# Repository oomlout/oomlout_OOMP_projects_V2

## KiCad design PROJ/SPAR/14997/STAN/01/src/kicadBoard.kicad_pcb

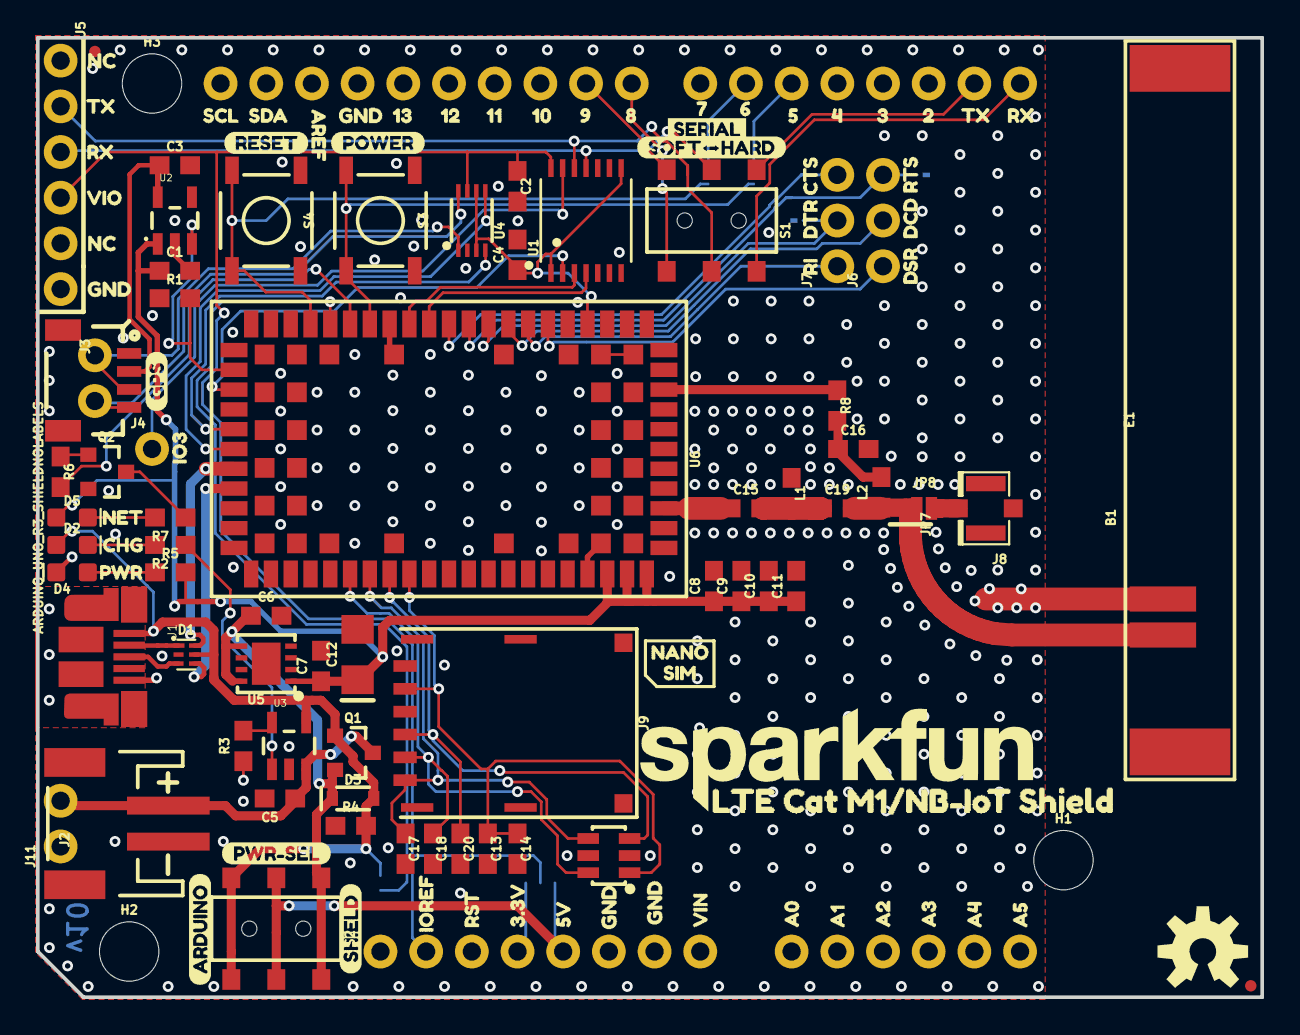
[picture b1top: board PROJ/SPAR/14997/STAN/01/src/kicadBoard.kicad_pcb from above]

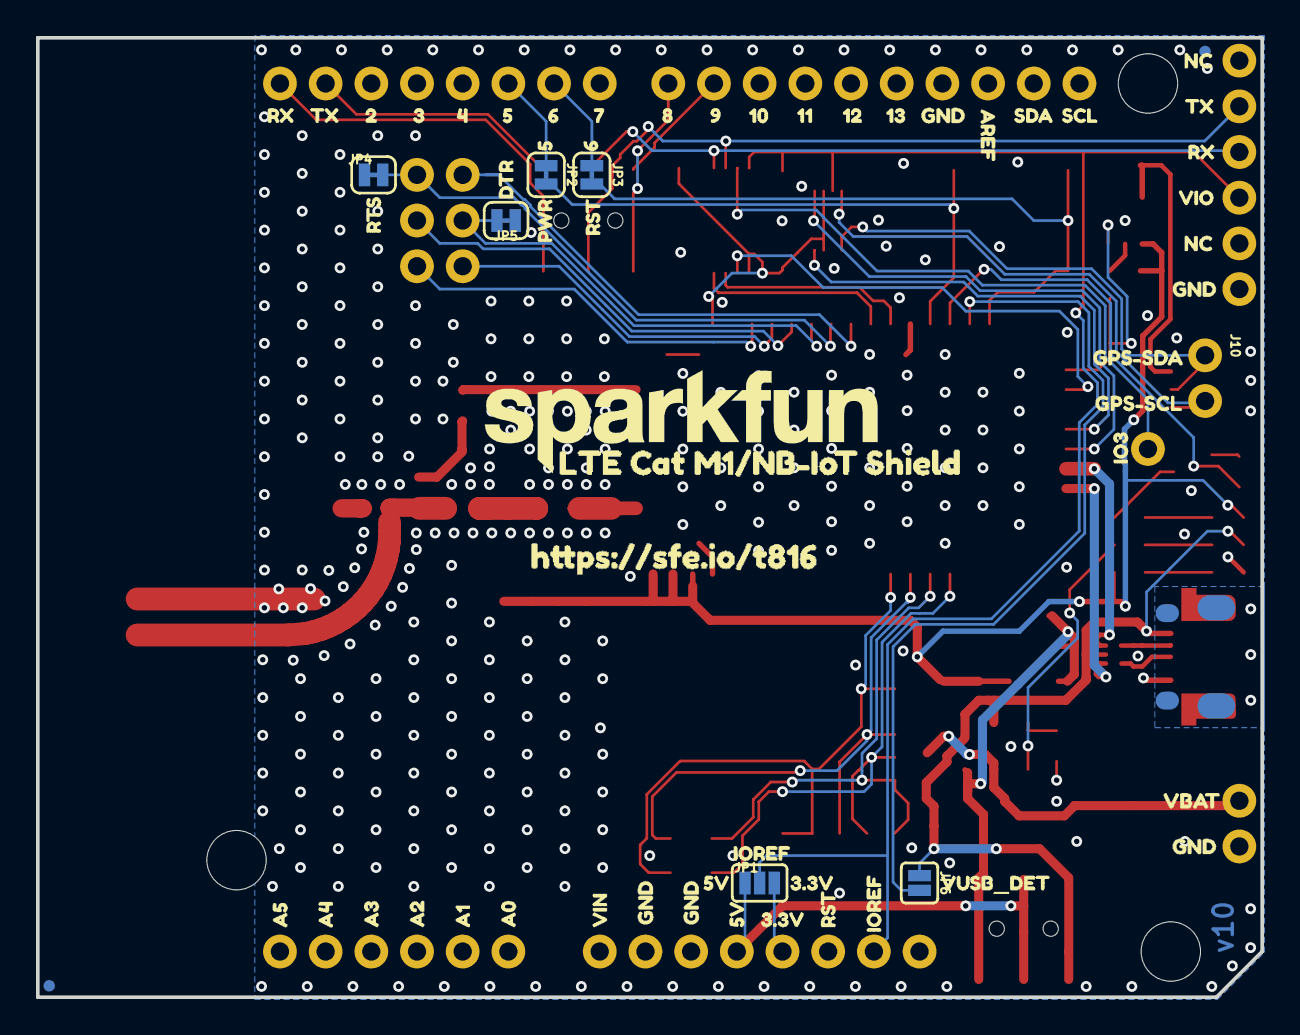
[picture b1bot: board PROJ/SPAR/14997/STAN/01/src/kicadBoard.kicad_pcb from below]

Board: 2 copper layers, 68.1 x 53.3 mm, 193 parts (64 on the bottom side), 60 nets.

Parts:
B1: ARDUINO_UNO_R3_SHIELDNOLABELS; UNO_R3_SHIELD_NOLABELS
C1, C3: 1.0uF; 0603
C2, C4, C8, C13: 0.1uF; 0603
C5, C6, C7: 4.7uF; 0603
C9: 10nF; 0603
C10, C15: 15pF; 0603
C11: 68pF; 0603
C12: 100uF; 1206-POLAR
C14, C17, C18, C20: 47pF; 0603
C16: DNP; 0603
C19: 0; 0603
D1: PRTR5V0U2F; SOT886
D2: Yellow; LED-0603
D3: 1A/23V/620mV; SOD-323
D4: RED; LED-0603
D5: BLUE; LED-0603
D6: DT1042-04SO-7; SOT23-6L
E1: MOLEX-146200; MOLEX_146200
FD1, FD2, FD3, FD4: FIDUCIALUFIDUCIAL; FIDUCIAL-MICRO
FRAME1, FRAME2: FRAME-LETTER; CREATIVE_COMMONS
H1, H2, H3: STAND-OFF
J1: USB-MICROB-PTH-MILL
J2: JST-2-SMD
J3: 1X04_1MM_RA
J4: 1X01_NO_SILK
J5: 1X06_NO_SILK
J6, J7: 1X03_NO_SILK
J8: U.FL
J9: NANO_SIM; NANO_SIM_WURTH_693043020611
J10, J11: 1X02_NO_SILK
JP1: IOREF-SEL; SMT-JUMPER_3_NO_SILK
JP2, JP3: JUMPER-SMT_2_NC_TRACE_SILK; SMT-JUMPER_2_NC_TRACE_SILK
JP4, JP5: SMT-JUMPER_2_NC_TRACE_SILK
JP6: VUSB_DET; SMT-JUMPER_2_NO_SILK
JP7: J-CHIP; SMT-JUMPER_2_NC_TRACE_NO-SILK
JP8: J-U.FL; SMT-JUMPER_2_NO_NO-SILK
L1: 39nH; 0603
L2: DNP; 0603
LOGO1, LOGO3: SFE_LOGO_NAME.2_INCH; SFE_LOGO_NAME_.2
LOGO2: OSHW-LOGOM; OSHW-LOGO-M
Q1: 2.5A/30V/105mΩ; SOT23-3
Q2: 600mA/40V; SOT23-3
R1: 47k; 0603
R2, R5, R7: 1k; 0603
R3: 2.0k; 0603
R4, R6: 10k; 0603
R8: DNP; 0603
S1, S2: SWITCH_DPDT_SMD_AYZ0202
S3: PWR_ON; TACTILE_SWITCH_SMD_5.2MM
S4: RESET; TACTILE_SWITCH_SMD_5.2MM
U1: TXB0104; TSSOP14
U2: AP2112K-3.3; SOT23-5
U3: MCP73831; SOT23-5
U4: TCA9406DCU; VSSOP-8
U5: AP7361C-33FGE; 8-UDFN
U6: SARA-R410M-2B; SARA-LGA
U$1, U$85: SCL0
U$2, U$84: SDA1
U$3, U$86: AREF2
U$4, U$45, U$46, U$73, U$74, U$88, U$104, U$105, U$112: GND3
U$5, U$87: 134
U$6, U$89: 125
U$7, U$90: 116
U$8, U$91: 107
U$9, U$92: 98
U$10, U$93: 89
U$11: RESET48
U$12: GPS47
U$13, U$94: 714
U$14, U$62, U$95: 615
U$15, U$61, U$96: 516
U$16, U$97: 417
U$17, U$98: 318
U$18, U$99: 219
U$19: POWER49
U$20, U$30, U$81, U$101: RX22
U$21, U$31, U$80, U$100: TX21
U$22: SERIAL57
U$23: CTS23
U$24, U$63: DTR24
U$25: RI25
U$26: DSR26
U$27: DCD27
U$28, U$64: RTS28
U$29, U$82: VIO29
U$32, U$77: LTE_CAT_M1#NB#IOT_SHIELD1
U$33: ARDUINO51
U$34, U$79: IO334
U$35: NET31
U$36: CHG33
U$37, U$59: PWR32
U$38: PWR#SEL53
U$39: SHIELD52
U$40, U$42: RST0
U$41, U$56, U$78: IOREF39
U$43, U$58, U$76: 3#3V41
U$44, U$57, U$75: 5V42
U$47, U$72: VIN43
U$48, U$71: A044
U$49, U$70: A145
U$50, U$69: A246
U$51, U$68: A347
U$52, U$67: A448
U$53, U$66: A549
U$54: NANO50
U$55: SIM51
U$60: RST40
U$65: VUSB_DET52
U$83: HTTPS###SFE#IO#T8160
U$102: SOFT#HARD50
U$103, U$106, U$107, U$108: NC0
U$109: GPS#SCL1
U$110: GPS#SDA0
U$111: VBAT2

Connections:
1.8V: C4.1, U1.1, U1.8, U4.3, U4.6, U6.4
3.3V: C1.1, C7.1, C8.1, C9.1, C10.1, C11.1, C12.1, D5.A, R5.2, U2.1, U5.1, U6.51, U6.52, U6.53
ANT: C15.1, U6.56
ANT_DET: R8.1, U6.62
ARDUINO-3.3V: B1.3.3V, JP1.3
ARDUINO-5V: B1.5V, JP1.1, S2.2, S2.5
CTS: J7.3, U6.11
D+: D1.4, U6.29
D-: D1.6, U6.28
DCD: J6.2, U6.8
DSR: J6.1, U6.6
DTR: J7.2, JP5.2, U6.9
GND: B1.AREF, B1.GND@0, B1.GND@1, B1.GND@2, C1.2, C2.2, C3.2, C4.2, C5.2, C6.2, C7.2, C8.2, C9.2, C10.2, C11.2, C12.2, C13.2, C14.2, C16.2, C17.2, C18.2, C20.2, D1.2, D4.C, D6.2, D6.5, E1.GND, J1.GND, J2.1, J3.1, J5.6, J8.1, J8.2, J9.C5, J11.1, JP4.1, JP5.1, L1.1, Q2.2, R1.1, R3.1, R4.1, S3.1, S3.2, S4.1, S4.2, U1.7, U2.2, U3.2, U4.2, U5.4, U5.EP, U6.1, U6.3, U6.5, U6.14, U6.20, U6.21, U6.22, U6.30, U6.32, U6.33, U6.43, U6.50, U6.54, U6.55, U6.57, U6.58, U6.59, U6.60, U6.61, U6.63, U6.64, U6.65, U6.66, U6.67, U6.68, U6.69, U6.70, U6.71, U6.72, U6.73, U6.74, U6.75, U6.76, U6.77, U6.78, U6.79, U6.80, U6.81, U6.82, U6.83, U6.84, U6.85, U6.86, U6.87, U6.88, U6.89, U6.90, U6.91, U6.92, U6.93, U6.94, U6.95, U6.96
GPIO1: R6.2, U6.16
GPIO2: R1.2, U2.3, U6.23
GPIO3-CELL: U1.2, U6.24
GPIO3-QWIIC: J4.1, U1.13
GPS-3.3V: C3.1, J3.2, U2.5
HARDRX-ARDUINO: B1.RX, S1.1
HARDTX-ARDUINO: B1.TX, S1.4
IOREF: B1.IOREF, C2.1, J5.4, JP1.2, U1.14, U4.7
unnamed: R3.2, U3.5
unnamed: C16.1, L2.2, R8.2
unnamed: C15.2, C19.1, L1.2
unnamed: J8.FEED, JP8.2
unnamed: Q2.1, R6.1
unnamed: D1.1, J1.D-
unnamed: D5.C, R7.2
unnamed: D1.3, J1.D+
unnamed: Q2.3, R7.1
unnamed: D4.A, R5.1
unnamed: D2.C, R2.2
unnamed: R2.1, U3.1
unnamed: B1.D5, JP2.1
unnamed: B1.D6, JP3.1
unnamed: C19.2, JP7.1, JP8.1, L2.1
unnamed: E1.FEED, JP7.2
PWR_ON: JP2.2, S3.3, S3.4, U6.15
RESET_N: JP3.2, S4.3, S4.4, U6.18
RI: J7.1, U6.7
RTS: J6.3, JP4.2, U6.10
RX-ARDUINO: J5.2, S1.2, U1.12
RX-CELL: U1.4, U6.12
SCL-CELL: U4.5, U6.27
SCL-QWIIC: J3.4, J10.2, U4.8
SDA-CELL: U4.4, U6.26
SDA-QWIIC: J3.3, J10.1, U4.1
SHIELD: J1.SHIELD, J1.SHIELD2, J1.SHIELD3, J1.SHIELD4, J1.SHIELD5, J1.SHIELD6, J1.SHIELD7, J1.SHIELD8, J1.SHIELD9, J1.SHIELD10
SIM_CLK: C18.1, D6.6, J9.C3, U6.38
SIM_IO: C17.1, D6.4, J9.C7, U6.39
SIM_RST: C20.1, D6.3, J9.C2, U6.40
SOFTRX-ARDUINO: B1.D8, S1.3
SOFTTX-ARDUINO: B1.D9, S1.6
TX-ARDUINO: J5.3, S1.5, U1.11
TX-CELL: U1.3, U6.13
VIN: C6.1, D3.C, Q1.2, S2.1, S2.4, U5.5, U5.8
VSIM: C13.1, C14.1, D6.1, J9.C1, U6.41
VUSB_DET: JP6.2, U6.17
V_BATT: C5.1, J2.2, J11.2, Q1.3, U3.3
V_USB: D1.5, D2.A, D3.A, J1.VBUS, JP6.1, Q1.1, R4.2, S2.3, S2.6, U3.4

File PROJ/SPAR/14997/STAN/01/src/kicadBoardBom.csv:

"Id";"Designator";"Package";"Quantity";"Designation";"Supplier and ref";
1;"U$16,U$97";"417";2;"";;;
2;"U$7,U$90";"116";2;"";;;
3;"J2";"JST-2-SMD";1;"";;;
4;"C12";"1206-POLAR";1;"100uF";;;
5;"FD4,FD3,FD2,FD1";"FIDUCIAL-MICRO";4;"FIDUCIALUFIDUCIAL";;;
6;"U$22";"SERIAL57";1;"";;;
7;"C11";"0603";1;"68pF";;;
8;"U$107,U$103,U$106,U$108";"NC0";4;"";;;
9;"U$26";"DSR26";1;"";;;
10;"U1";"TSSOP14";1;"TXB0104";;;
11;"U$1,U$85";"SCL0";2;"";;;
12;"D6";"SOT23-6L";1;"DT1042-04SO-7";;;
13;"U$9,U$92";"98";2;"";;;
14;"H1,H2,H3";"STAND-OFF";3;"STAND-OFF";;;
15;"C5,C7,C6";"0603";3;"4.7uF";;;
16;"U$37,U$59";"PWR32";2;"";;;
17;"U$54";"NANO50";1;"";;;
18;"U$4,U$46,U$45,U$104,U$73,U$112,U$88,U$105,U$74";"GND3";9;"";;;
19;"U$20,U$30,U$81,U$101";"RX22";4;"";;;
20;"U4";"VSSOP-8";1;"TCA9406DCU";;;
21;"L2,C16,R8";"0603";3;"DNP";;;
22;"LOGO2";"OSHW-LOGO-M";1;"OSHW-LOGOM";;;
23;"U$2,U$84";"SDA1";2;"";;;
24;"LOGO1,LOGO3";"SFE_LOGO_NAME_.2";2;"SFE_LOGO_NAME.2_INCH";;;
25;"U$41,U$78,U$56";"IOREF39";3;"";;;
26;"U$24,U$63";"DTR24";2;"";;;
27;"C15,C10";"0603";2;"15pF";;;
28;"C18,C20,C17,C14";"0603";4;"47pF";;;
29;"U$43,U$76,U$58";"3#3V41";3;"";;;
30;"JP8";"SMT-JUMPER_2_NO_NO-SILK";1;"J-U.FL";;;
31;"U$18,U$99";"219";2;"";;;
32;"J7,J6";"1X03_NO_SILK";2;"";;;
33;"FRAME2,FRAME1";"CREATIVE_COMMONS";2;"FRAME-LETTER";;;
34;"U$51,U$68";"A347";2;"";;;
35;"C13,C8,C2,C4";"0603";4;"0.1uF";;;
36;"U$21,U$31,U$80,U$100";"TX21";4;"";;;
37;"U$12";"GPS47";1;"";;;
38;"U$28,U$64";"RTS28";2;"";;;
39;"U$53,U$66";"A549";2;"";;;
40;"U$52,U$67";"A448";2;"";;;
41;"R1";"0603";1;"47k";;;
42;"D3";"SOD-323";1;"1A/23V/620mV";;;
43;"U$47,U$72";"VIN43";2;"";;;
44;"U$14,U$62,U$95";"615";3;"";;;
45;"B1";"UNO_R3_SHIELD_NOLABELS";1;"ARDUINO_UNO_R3_SHIELDNOLABELS";;;
46;"E1";"MOLEX_146200";1;"MOLEX-146200";;;
47;"U$27";"DCD27";1;"";;;
48;"U$23";"CTS23";1;"";;;
49;"U$38";"PWR#SEL53";1;"";;;
50;"U$10,U$93";"89";2;"";;;
51;"D4";"LED-0603";1;"RED";;;
52;"U6";"SARA-LGA";1;"SARA-R410M-2B";;;
53;"U$15,U$96,U$61";"516";3;"";;;
54;"U$17,U$98";"318";2;"";;;
55;"U$39";"SHIELD52";1;"";;;
56;"JP7";"SMT-JUMPER_2_NC_TRACE_NO-SILK";1;"J-CHIP";;;
57;"J9";"NANO_SIM_WURTH_693043020611";1;"NANO_SIM";;;
58;"J11,J10";"1X02_NO_SILK";2;"";;;
59;"U$8,U$91";"107";2;"";;;
60;"R6,R4";"0603";2;"10k";;;
61;"U$3,U$86";"AREF2";2;"";;;
62;"U$5,U$87";"134";2;"";;;
63;"U3";"SOT23-5";1;"MCP73831";;;
64;"U$50,U$69";"A246";2;"";;;
65;"J1";"USB-MICROB-PTH-MILL";1;"";;;
66;"U$33";"ARDUINO51";1;"";;;
67;"Q1";"SOT23-3";1;"2.5A/30V/105mΩ";;;
68;"D5";"LED-0603";1;"BLUE";;;
69;"U$44,U$57,U$75";"5V42";3;"";;;
70;"S3";"TACTILE_SWITCH_SMD_5.2MM";1;"PWR_ON";;;
71;"U5";"8-UDFN";1;"AP7361C-33FGE";;;
72;"C9";"0603";1;"10nF";;;
73;"U$29,U$82";"VIO29";2;"";;;
74;"R3";"0603";1;"2.0k";;;
75;"C19";"0603";1;"0";;;
76;"U$48,U$71";"A044";2;"";;;
77;"U$13,U$94";"714";2;"";;;
78;"R5,R2,R7";"0603";3;"1k";;;
79;"C1,C3";"0603";2;"1.0uF";;;
80;"J8";"U.FL";1;"U.FL";;;
81;"Q2";"SOT23-3";1;"600mA/40V";;;
82;"U$25";"RI25";1;"";;;
83;"D1";"SOT886";1;"PRTR5V0U2F";;;
84;"U$49,U$70";"A145";2;"";;;
85;"J3";"1X04_1MM_RA";1;"";;;
86;"U$102";"SOFT#HARD50";1;"";;;
87;"U$11";"RESET48";1;"";;;
88;"U$77,U$32";"LTE_CAT_M1#NB#IOT_SHIELD1";2;"";;;
89;"S1,S2";"SWITCH_DPDT_SMD_AYZ0202";2;"";;;
90;"L1";"0603";1;"39nH";;;
91;"U$34,U$79";"IO334";2;"";;;
92;"U2";"SOT23-5";1;"AP2112K-3.3";;;
93;"J5";"1X06_NO_SILK";1;"";;;
94;"U$19";"POWER49";1;"";;;
95;"D2";"LED-0603";1;"Yellow";;;
96;"U$55";"SIM51";1;"";;;
97;"J4";"1X01_NO_SILK";1;"";;;
98;"U$6,U$89";"125";2;"";;;
99;"U$35";"NET31";1;"";;;
100;"U$36";"CHG33";1;"";;;
101;"U$40,U$42";"RST0";2;"";;;
102;"S4";"TACTILE_SWITCH_SMD_5.2MM";1;"RESET";;;
103;"U$111";"VBAT2";1;"";;;
104;"JP1";"SMT-JUMPER_3_NO_SILK";1;"IOREF-SEL";;;
105;"U$60";"RST40";1;"";;;
106;"JP5,JP4";"SMT-JUMPER_2_NC_TRACE_SILK";2;"";;;
107;"JP3,JP2";"SMT-JUMPER_2_NC_TRACE_SILK";2;"JUMPER-SMT_2_NC_TRACE_SILK";;;
108;"JP6";"SMT-JUMPER_2_NO_SILK";1;"VUSB_DET";;;
109;"U$110";"GPS#SDA0";1;"";;;
110;"U$65";"VUSB_DET52";1;"";;;
111;"U$109";"GPS#SCL1";1;"";;;
112;"U$83";"HTTPS###SFE#IO#T8160";1;"";;;

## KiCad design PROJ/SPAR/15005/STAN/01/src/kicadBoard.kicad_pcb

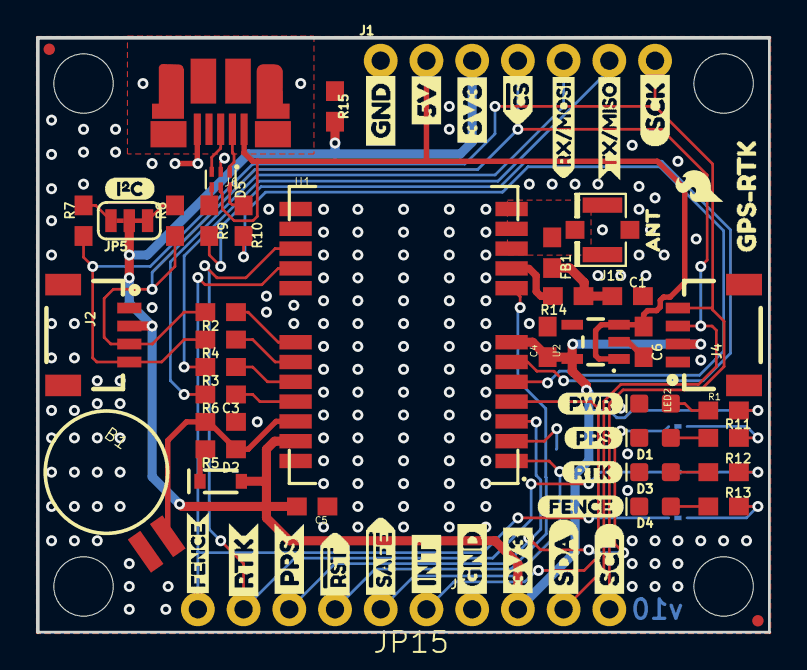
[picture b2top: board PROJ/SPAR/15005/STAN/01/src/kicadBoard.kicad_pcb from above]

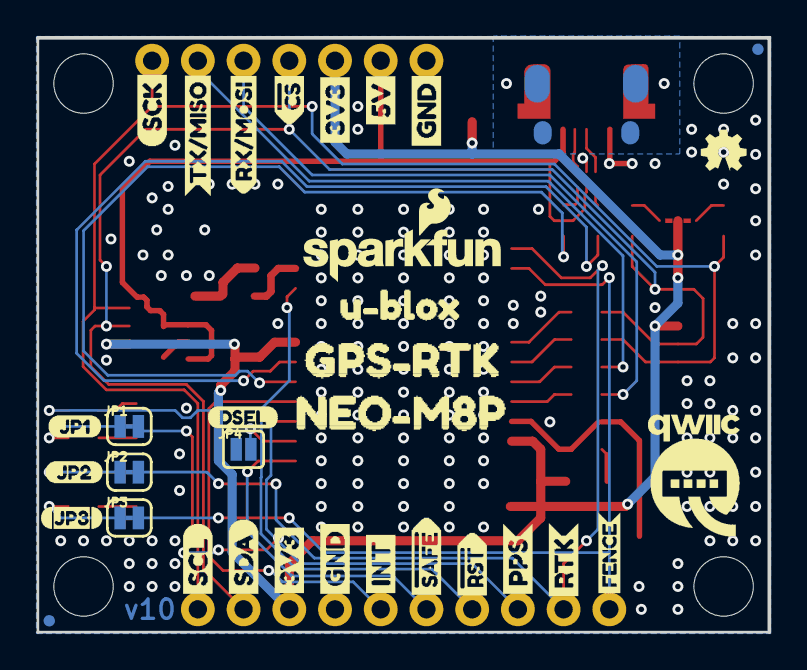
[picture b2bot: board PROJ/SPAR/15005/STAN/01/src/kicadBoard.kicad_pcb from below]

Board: 2 copper layers, 40.6 x 33.0 mm, 103 parts (33 on the bottom side), 39 nets.

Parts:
B1: 6.8MM_COIN_CELL; BATTCON-6.8MM
C1: 47pF; 0603
C3, C4, C6: 1.0uF; 0603
C5: 0.1uF; 0603
D1: Yellow; LED-0603
D2: 0.5A/40V/420mV; SOD-323
D3: GREEN; LED-0603
D4: BLUE; LED-0603
D5: PRTR5V0U2F; SOT886
FB1: 30Ω/1.8A; 0603
FRAME1: FRAME-LETTER; CREATIVE_COMMONS
J1: 1X07_NO_SILK
J2, J4: Qwiic Right Angle; 1X04_1MM_RA
J3: PTH; 1X04_NO_SILK
J6: USB-MICROB-PTH-MILL
J13: U.FL
JP1, JP2, JP3: SMT-JUMPER_2_NC_TRACE_SILK
JP4: SMT-JUMPER_2_NO_SILK
JP5: SMT-JUMPER_3_2-NC_TRACE_SILK
JP15: 1X06_NO_SILK
JP21, JP61, JP71, JP81: FIDUCIALUFIDUCIAL; MICRO-FIDUCIAL
JP31, JP41, JP91, JP101: STAND-OFF
LED2: RED; LED-0603
LOGO1: OSHW-LOGOMINI; OSHW-LOGO-MINI
LOGO2: SFE_LOGO_NAME_FLAME.1_INCH; SFE_LOGO_NAME_FLAME_.1
R1, R5, R11, R12, R13: 1k; 0603
R2, R3, R4, R6: 33; 0603
R7, R8: 2.2k; 0603
R9, R10: 27; 0603
R14: 10; 0603
R15: 100k; 0603
U1: NEO-M8P
U2: 3.3V; SOT23-5
U$1, U$4: SDA-[)
U$3, U$5: SCL-[)
U$6, U$7, U$60, U$61: 3V3-04
U$8, U$9, U$62, U$63: GND-04
U$10: I_SUPER2_C-()-03
U$11: FENCE2
U$12: JP20
U$13, U$28, U$29: RTK1
U$14, U$17: FENCE0
U$15, U$16: INT8
U$18: PWR-()-03
U$19, U$20: 5V
U$21: GPS#RTK0
U$22: U#BLOX3
U$23, U$24: CS#-_]
U$25: JP10
U$26: RX#MOSI2
U$27: DSEL0
U$30: QWIIC-LOGO-MEDIUM
U$31: RX#MOSI3
U$32: JP32
U$33: SFE_LOGO_FLAME_.1
U$34: TX#MISO0
U$35, U$36: #RST3
U$37: TX#MISO1
U$38, U$41: SCK-(]-04
U$39, U$40: #SAFE1
U$43, U$44: PPS5
U$52: PPS0
U$53: NEO#M8P3
U$54: GPS#RTK1
U$55: ANT0

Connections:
3.3V: C4.1, C5.2, D2.A, J1.3, J2.2, J3.2, J4.2, JP5.2, R1.2, R15.2, U1.7, U1.23, U2.5
5V: C6.1, D5.5, J1.2, J6.VBUS, U2.1, U2.3
ANT_VCC: C1.1, FB1.2, R14.1
BACKUP: B1.+, C3.1, R5.1, U1.22
D+: D5.4, R9.1
D-: D5.6, R10.1
D_SEL: JP4.2, U1.2
FENCE_STAT: JP3.2, JP15.6, U1.16
GND: B1.-, C1.2, C3.2, C4.2, C5.1, C6.2, D1.C, D3.C, D4.C, D5.2, J1.1, J2.1, J3.1, J4.1, J6.GND, J13.1, J13.2, JP4.1, LED2.C, R15.1, U1.10, U1.12, U1.13, U1.24, U2.2
GPS_ANT1: FB1.1, J13.FEED, U1.11
INT: JP15.1, U1.4
unnamed: D3.A, R12.1
unnamed: D1.A, R11.1
unnamed: JP2.1, R12.2
unnamed: JP1.1, R11.2
unnamed: JP5.1, R8.2
unnamed: D2.C, R5.2
unnamed: D4.A, R13.1
unnamed: JP5.3, R7.2
unnamed: JP3.1, R13.2
unnamed: LED2.A, R1.1
unnamed: R9.2, U1.6
unnamed: R10.2, U1.5
unnamed: R14.2, U1.9
PPS: JP1.2, JP15.4, U1.3
RTK_STAT: JP2.2, JP15.5, U1.15
RXI/MOSI: J1.5, R6.2
RXLV: R6.1, U1.21
SCL/SCK: J1.7, J2.4, J3.4, J4.4, R4.2, R7.1
SCL_LV: R4.1, U1.19
SDA/~CS: J1.4, J2.3, J3.3, J4.3, R2.2, R8.1
SDA_LV: R2.1, U1.18
SHLD: J6.SHIELD, J6.SHIELD2, J6.SHIELD3, J6.SHIELD4, J6.SHIELD5, J6.SHIELD6, J6.SHIELD7, J6.SHIELD8, J6.SHIELD9, J6.SHIELD10
TXLV: R3.1, U1.20
TXO/MISO: J1.6, R3.2
USB_D+: D5.3, J6.D+
USB_D-: D5.1, J6.D-
~RESET: JP15.3, U1.8
~SAFE: JP15.2, U1.1

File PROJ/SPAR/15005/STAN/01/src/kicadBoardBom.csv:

"Id";"Designator";"Package";"Quantity";"Designation";"Supplier and ref";
1;"J13";"U.FL";1;"U.FL";;;
2;"U1";"NEO-M8P";1;"NEO-M8P";;;
3;"U$6,U$61,U$7,U$60";"3V3-04";4;"";;;
4;"C6,C3,C4";"0603";3;"1.0uF";;;
5;"D2";"SOD-323";1;"0.5A/40V/420mV";;;
6;"U$10";"I_SUPER2_C-()-03";1;"";;;
7;"FRAME1";"CREATIVE_COMMONS";1;"FRAME-LETTER";;;
8;"R4,R6,R2,R3";"0603";4;"33";;;
9;"U$13,U$29,U$28";"RTK1";3;"";;;
10;"JP21,JP61,JP81,JP71";"MICRO-FIDUCIAL";4;"FIDUCIALUFIDUCIAL";;;
11;"D4";"LED-0603";1;"BLUE";;;
12;"J1";"1X07_NO_SILK";1;"";;;
13;"U$23,U$24";"CS#-_]";2;"";;;
14;"R13,R11,R1,R5,R12";"0603";5;"1k";;;
15;"J3";"1X04_NO_SILK";1;"PTH";;;
16;"U$8,U$63,U$62,U$9";"GND-04";4;"";;;
17;"U$38,U$41";"SCK-(]-04";2;"";;;
18;"C5";"0603";1;"0.1uF";;;
19;"JP91,JP41,JP101,JP31";"STAND-OFF";4;"STAND-OFF";;;
20;"U$1,U$4";"SDA-[)";2;"";;;
21;"U$35,U$36";"#RST3";2;"";;;
22;"D1";"LED-0603";1;"Yellow";;;
23;"B1";"BATTCON-6.8MM";1;"6.8MM_COIN_CELL";;;
24;"C1";"0603";1;"47pF";;;
25;"JP5";"SMT-JUMPER_3_2-NC_TRACE_SILK";1;"";;;
26;"R8,R7";"0603";2;"2.2k";;;
27;"FB1";"0603";1;"30Ω/1.8A";;;
28;"U$3,U$5";"SCL-[)";2;"";;;
29;"U$52";"PPS0";1;"";;;
30;"J6";"USB-MICROB-PTH-MILL";1;"";;;
31;"U$19,U$20";"5V";2;"";;;
32;"U$21";"GPS#RTK0";1;"";;;
33;"U$11";"FENCE2";1;"";;;
34;"U$33";"SFE_LOGO_FLAME_.1";1;"";;;
35;"U$15,U$16";"INT8";2;"";;;
36;"U$26";"RX#MOSI2";1;"";;;
37;"U$43,U$44";"PPS5";2;"";;;
38;"U$18";"PWR-()-03";1;"";;;
39;"J4,J2";"1X04_1MM_RA";2;"Qwiic Right Angle";;;
40;"R9,R10";"0603";2;"27";;;
41;"U$34";"TX#MISO0";1;"";;;
42;"D5";"SOT886";1;"PRTR5V0U2F";;;
43;"U$55";"ANT0";1;"";;;
44;"U$39,U$40";"#SAFE1";2;"";;;
45;"R15";"0603";1;"100k";;;
46;"U2";"SOT23-5";1;"3.3V";;;
47;"R14";"0603";1;"10";;;
48;"LED2";"LED-0603";1;"RED";;;
49;"U$14,U$17";"FENCE0";2;"";;;
50;"D3";"LED-0603";1;"GREEN";;;
51;"JP15";"1X06_NO_SILK";1;"";;;
52;"JP3,JP2,JP1";"SMT-JUMPER_2_NC_TRACE_SILK";3;"";;;
53;"LOGO1";"OSHW-LOGO-MINI";1;"OSHW-LOGOMINI";;;
54;"U$31";"RX#MOSI3";1;"";;;
55;"LOGO2";"SFE_LOGO_NAME_FLAME_.1";1;"SFE_LOGO_NAME_FLAME.1_INCH";;;
56;"JP4";"SMT-JUMPER_2_NO_SILK";1;"";;;
57;"U$12";"JP20";1;"";;;
58;"U$25";"JP10";1;"";;;
59;"U$37";"TX#MISO1";1;"";;;
60;"U$30";"QWIIC-LOGO-MEDIUM";1;"";;;
61;"U$54";"GPS#RTK1";1;"";;;
62;"U$32";"JP32";1;"";;;
63;"U$53";"NEO#M8P3";1;"";;;
64;"U$27";"DSEL0";1;"";;;
65;"U$22";"U#BLOX3";1;"";;;

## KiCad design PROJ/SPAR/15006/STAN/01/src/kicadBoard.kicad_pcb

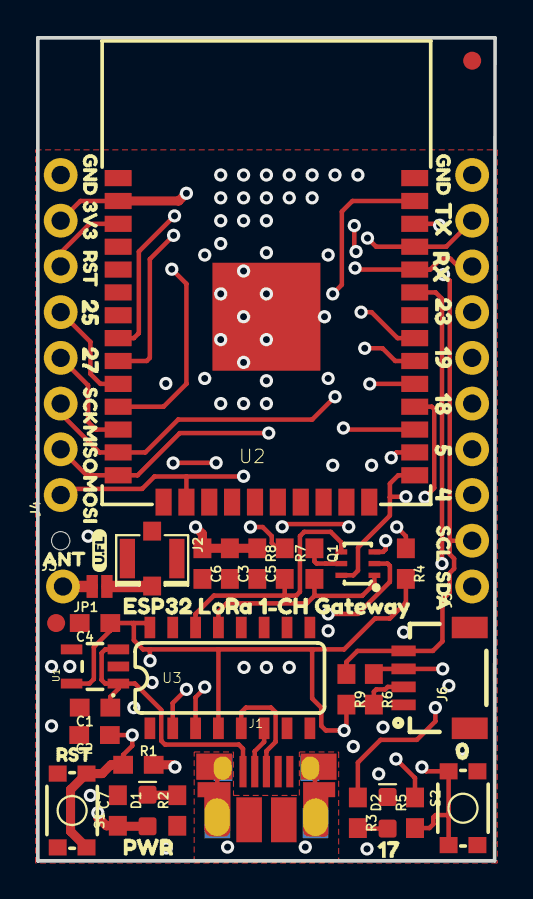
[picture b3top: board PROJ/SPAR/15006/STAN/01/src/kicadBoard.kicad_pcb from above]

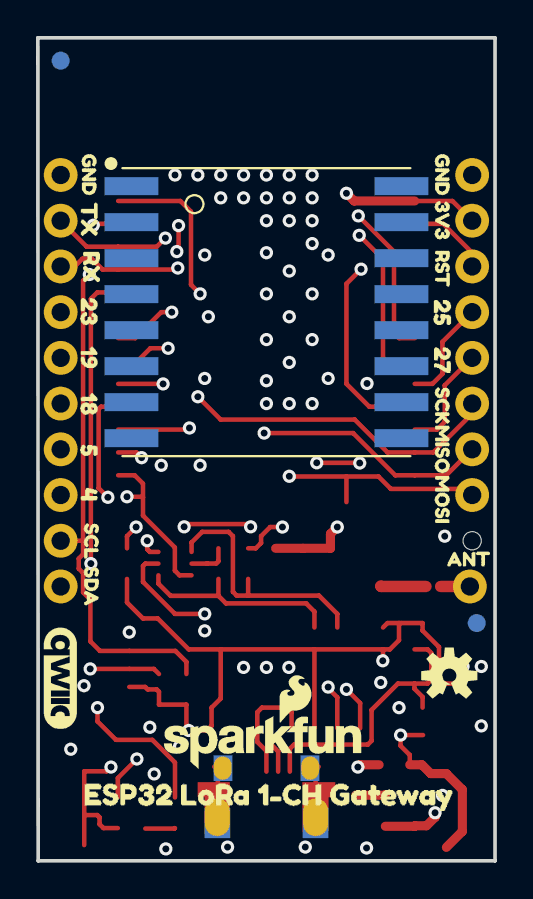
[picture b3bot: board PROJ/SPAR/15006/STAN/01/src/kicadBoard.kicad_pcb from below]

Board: 4 copper layers, 25.4 x 45.7 mm, 87 parts (26 on the bottom side), 36 nets.

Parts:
@HOLE0: (no value)
C1, C4: 1.0uF; 0603
C2, C3, C7: 0.1uF; 0603
C5: 10uF; 0603
C6: 4.7uF; 0603
D1: RED; LED-0603
D2: BLUE; LED-0603
FD1, FD2, FD3, FD4: FIDUCIAL1X2; FIDUCIAL-1X2
FRAME1: FRAME-LETTER; CREATIVE_COMMONS
J1: USB; USB-MICROB-PTH-MILL
J2: U.FL
J3: 1X01_NO_SILK
J4: 1X08_NO_SILK
J5: 1X10_NO_SILK
J6: QWIIC; 1X04_1MM_RA
JP1: Ant Sel; SMT-JUMPER_2_NO_NO-SILK
LOGO1: REVISION
LOGO2: SFE_LOGO_NAME_FLAME.1_INCH; SFE_LOGO_NAME_FLAME_.1
LOGO3: OSHW-LOGOS; OSHW-LOGO-S
Q1: MBT3904DW1T1; SC70-6
R1, R4, R5, R7, R8: 10k; 0603
R2, R3: 1k; 0603
R6, R9: 2.2k; 0603
S1: RESET; TACTILE_SWITCH_SMD_4.6X2.8MM
S2: 0; TACTILE_SWITCH_SMD_4.6X2.8MM
U1: 3.3V; SOT23-5
U2: ESP-WROOM-32NARROW; ESP-WROOM-32-NARROW
U3: CH340C; SO016
U4: RFM95W; RFM95_96_97_98W
U$1, U$10, U$26, U$37: GND0
U$2, U$38: 3V31
U$3, U$20, U$39: RST2
U$4, U$40: 2517
U$5, U$41: 279
U$6, U$42: SCK3
U$7, U$43: MISO4
U$8, U$44: MOSI5
U$9, U$36: ANT6
U$11, U$27: TX16
U$12, U$28: RX15
U$13, U$29: 2314
U$14, U$30: 1912
U$15, U$31: 1811
U$16, U$32: 513
U$17, U$33: 410
U$18, U$34: SCL8
U$19, U$35: SDA7
U$21: 020
U$22: PWR19
U$23: 1722
U$24: U#FL0
U$25: ESP32_LORA_1#CH_GATEWAY21
U$45: ESP32_LORA_1#CH_GATEWAY23
U$46: QWIIC_COPYRIGHT_SMALL

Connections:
0: Q1.6, R5.1, S2.3, S2.4, U2.25
3.3V: C3.1, C4.1, C5.1, C6.1, C7.1, D1.A, J4.7, J6.2, R1.2, R4.2, R5.2, R6.2, R9.2, U1.5, U2.2, U3.4, U3.16, U4.3.3V
ANT: J3.1, JP1.2, U4.ANT
D+: J1.D+, U3.5
D-: J1.D-, U3.6
GND: C1.2, C2.2, C3.2, C4.2, C5.2, C6.2, C7.2, D2.C, J1.GND, J2.1, J2.2, J4.8, J5.10, J6.1, R2.1, S1.1, S1.2, S2.1, S2.2, U1.2, U2.1, U2.15, U2.38, U2.GND, U3.1, U4.GND@1, U4.GND@2, U4.GND@3
IO4: J5.3, U2.26
IO5: J5.4, U2.29
IO17: R3.1, U2.28
IO18: J5.5, U2.30
IO19: J5.6, U2.31
IO23: J5.7, U2.37
IO25: J4.5, U2.10
IO27: J4.4, U2.12
MISO: J4.2, U2.14, U4.MISO
MOSI: J4.1, U2.16, U4.MOSI
unnamed: D1.C, R2.2
unnamed: D2.A, R3.2
unnamed: J2.FEED, JP1.1
unnamed: Q1.5, R7.2
unnamed: Q1.2, R8.2
RESET: C2.1, J4.6, Q1.3, R1.1, S1.3, S1.4, U2.3
RFM_CS: U2.27, U4.NSS
RFM_DIO1/33: U2.9, U4.DIO1
RFM_DIO2/32: U2.8, U4.DIO2
RFM_INT/26: U2.11, U4.DIO0
RFM_RST: R4.1, U4.!RESET
RXI: J5.8, U2.34, U3.2
SCK: J4.3, U2.13, U4.SCK
SCL: J5.2, J6.4, R9.1, U2.36
SDA: J5.1, J6.3, R6.1, U2.33
SHIELD: J1.SHIELD, J1.SHIELD2, J1.SHIELD3, J1.SHIELD4, J1.SHIELD5, J1.SHIELD6, J1.SHIELD7, J1.SHIELD8, J1.SHIELD9, J1.SHIELD10
TXO: J5.9, U2.35, U3.3
V_USB: C1.1, J1.VBUS, U1.1, U1.3
~DTR: Q1.1, R7.1, U3.13
~RTS: Q1.4, R8.1, U3.14

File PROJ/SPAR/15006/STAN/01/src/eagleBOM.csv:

"Part";"Value";"Device";"Package";"Description";"PROD_ID";"SF_ID";"VALUE";
"C1";"1.0uF";"1.0UF-0603-16V-10%";"0603";"1µF ceramic capacitors";"CAP-00868";"";"1.0uF";
"C2";"0.1uF";"0.1UF-0603-25V-(+80/-20%)";"0603";"0.1µF ceramic capacitors";"CAP-00810";"";"0.1uF";
"C3";"0.1uF";"0.1UF-0603-25V-(+80/-20%)";"0603";"0.1µF ceramic capacitors";"CAP-00810";"";"0.1uF";
"C4";"1.0uF";"1.0UF-0603-16V-10%";"0603";"1µF ceramic capacitors";"CAP-00868";"";"1.0uF";
"C5";"10uF";"10UF-0603-6.3V-20%";"0603";"10.0µF ceramic capacitors";"CAP-11015";"";"10uF";
"C6";"4.7uF";"4.7UF-0603-6.3V-(10%)";"0603";"4.7µF ceramic capacitors";"CAP-08280";"";"4.7uF";
"C7";"0.1uF";"0.1UF-0603-25V-5%";"0603";"0.1µF ceramic capacitors";"CAP-08604";"";"0.1uF";
"D1";"RED";"LED-RED0603";"LED-0603";"Red SMD LED";"DIO-00819";"";"RED";
"D2";"BLUE";"LED-BLUE0603";"LED-0603";"Blue SMD LED";"DIO-08575";"";"BLUE";
"FD1";"FIDUCIAL1X2";"FIDUCIAL1X2";"FIDUCIAL-1X2";"Fiducial Alignment Points";"";"";"";
"FD2";"FIDUCIAL1X2";"FIDUCIAL1X2";"FIDUCIAL-1X2";"Fiducial Alignment Points";"";"";"";
"FD3";"FIDUCIAL1X2";"FIDUCIAL1X2";"FIDUCIAL-1X2";"Fiducial Alignment Points";"";"";"";
"FD4";"FIDUCIAL1X2";"FIDUCIAL1X2";"FIDUCIAL-1X2";"Fiducial Alignment Points";"";"";"";
"FRAME1";"FRAME-LETTER";"FRAME-LETTER";"CREATIVE_COMMONS";"Schematic Frame - Letter";"";"";"";
"J1";"USB";"USB_MICRO-B_HALF_PTH_MILL";"USB-MICROB-PTH-MILL";"USB Type Micro-B Connector";"CONN-13711";"";"";
"J2";"U.FL";"U.FL";"U.FL";"SMD Antenna Connector - U.FL";"CONN-09193";"WRL-09144";"U.FL";
"J3";"";"CONN_01PTH_NO_SILK_YES_STOP";"1X01_NO_SILK";"Single connection point. Often used as Generic Header-pin footprint for 0.1 inch spaced/style header connections";"";"";"";
"J4";"";"CONN_08NO_SILK_FEMALE_PTH";"1X08_NO_SILK";"Multi connection point. Often used as Generic Header-pin footprint for 0.1 inch spaced/style header connections";"CONN-08438";"";"";
"J5";"";"CONN_10NO_SILK_PTH_FEMALE";"1X10_NO_SILK";"Multi connection point. Often used as Generic Header-pin footprint for 0.1 inch spaced/style header connections";"CONN-11563";"";"";
"J6";"QWIIC";"QWIIC_CONNECTORJS-1MM";"1X04_1MM_RA";"SparkFun I2C Standard Qwiic Connector";"CONN-13694";"";"";
"JP1";"Ant Sel";"JUMPER-SMT_2_NO_NO-SILK";"SMT-JUMPER_2_NO_NO-SILK";"Normally open jumper";"";"";"";
"LOGO1";"REVISION";"REVISION";"REVISION";""Revision By" Text";"";"";"";
"LOGO2";"SFE_LOGO_NAME_FLAME.1_INCH";"SFE_LOGO_NAME_FLAME.1_INCH";"SFE_LOGO_NAME_FLAME_.1";"SparkFun Font Logo w/ Flame";"";"";"";
"LOGO3";"OSHW-LOGOS";"OSHW-LOGOS";"OSHW-LOGO-S";"Open-Source Hardware (OSHW) Logo";"";"";"";
"Q1";"MBT3904DW1T1";"TRANS_NPN_DUAL-MBT3904DW1T1";"SC70-6";"Dual NPN Transistors in Single Package";"TRANS-13337";"";"";
"R1";"10k";"10KOHM-0603-1/10W-1%";"0603";"10kΩ resistor";"RES-00824";"";"10k";
"R2";"1k";"1KOHM-0603-1/10W-1%";"0603";"1kΩ resistor";"RES-07856";"";"1k";
"R3";"1k";"1KOHM-0603-1/10W-1%";"0603";"1kΩ resistor";"RES-07856";"";"1k";
"R4";"10k";"10KOHM-0603-1/10W-1%";"0603";"10kΩ resistor";"RES-00824";"";"10k";
"R5";"10k";"10KOHM-0603-1/10W-1%";"0603";"10kΩ resistor";"RES-00824";"";"10k";
"R6";"2.2k";"2.2KOHM-0603-1/10W-1%";"0603";"2.2kΩ resistor";"RES-08272";"";"2.2k";
"R7";"10k";"10KOHM-0603-1/10W-1%";"0603";"10kΩ resistor";"RES-00824";"";"10k";
"R8";"10k";"10KOHM-0603-1/10W-1%";"0603";"10kΩ resistor";"RES-00824";"";"10k";
"R9";"2.2k";"2.2KOHM-0603-1/10W-1%";"0603";"2.2kΩ resistor";"RES-08272";"";"2.2k";
"S1";"RESET";"MOMENTARY-SWITCH-SPST-SMD-4.6X2.8MM";"TACTILE_SWITCH_SMD_4.6X2.8MM";"Momentary Switch (Pushbutton) - SPST";"SWCH-15606";"";"";
"S2";"0";"MOMENTARY-SWITCH-SPST-SMD-4.6X2.8MM";"TACTILE_SWITCH_SMD_4.6X2.8MM";"Momentary Switch (Pushbutton) - SPST";"SWCH-15606";"";"";
"U1";"3.3V";"V_REG_AP2112K-3.3V";"SOT23-5";"AP2112 - 600mA CMOS LDO Regulator w/ Enable";"VREG-12457";"";"3.3V";
"U2";"ESP-WROOM-32NARROW";"ESP-WROOM-32NARROW";"ESP-WROOM-32-NARROW";"";"IC-15676";"";"";
"U3";"CH340C";"CH340C";"SO016";"";"IC-14038";"";"";
"U4";"RFM95W";"RFM95W";"RFM95/96/97/98W";"RFM95/96/97/98";"IC-13959";"";"";

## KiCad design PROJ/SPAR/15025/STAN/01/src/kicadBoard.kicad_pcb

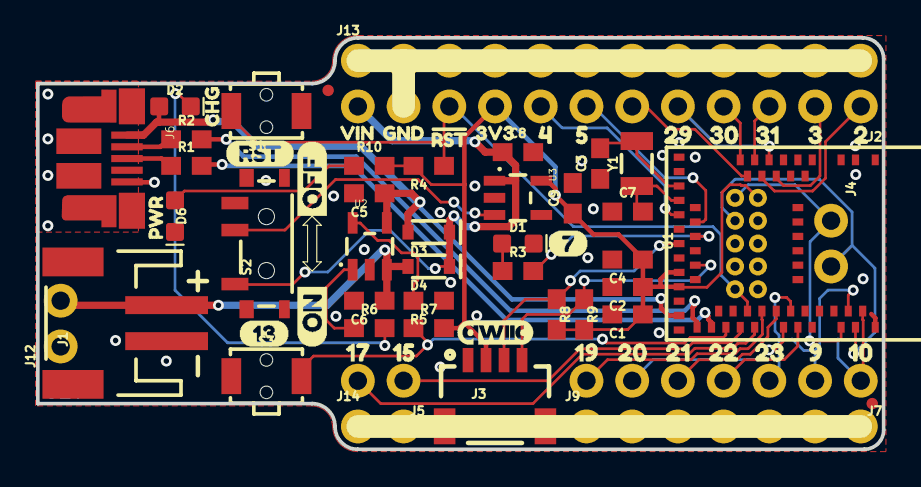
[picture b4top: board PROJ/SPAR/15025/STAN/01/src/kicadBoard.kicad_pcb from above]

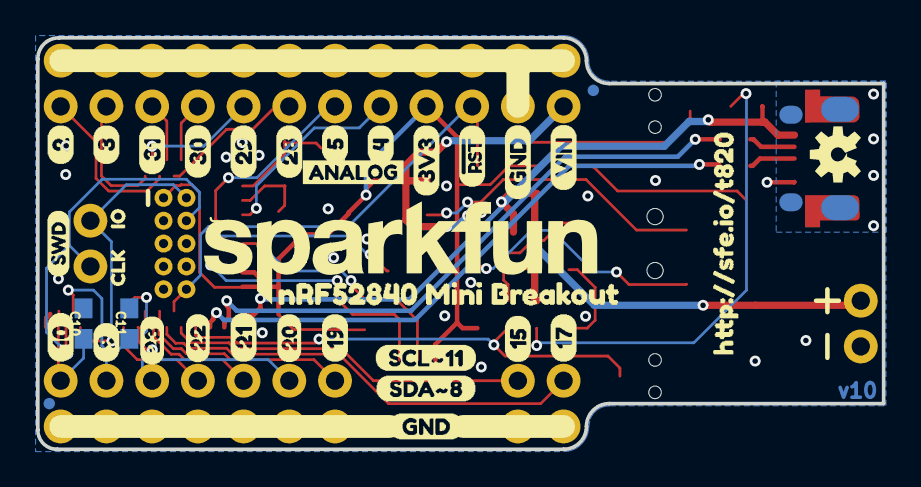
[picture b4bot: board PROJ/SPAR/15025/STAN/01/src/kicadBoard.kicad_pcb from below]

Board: 2 copper layers, 47.0 x 22.9 mm, 110 parts (37 on the bottom side), 42 nets.

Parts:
C1, C4: 10uF; 0603
C2: 0.1uF; 0603
C3, C7: 15pF; 0603
C5, C6: 4.7uF; 0603
C8, C9: 1.0uF; 0603
C10, C11: DNP; 0603
D1: BLUE; LED-0603
D2: Yellow; LED-0603
D3, D4: 1A/23V/620mV; SOD-323
D6: RED; LED-0603
FD1, FD2, FD3, FD4: FIDUCIALUFIDUCIAL; FIDUCIAL-MICRO
FRAME1: FRAME-LETTER; CREATIVE_COMMONS
J1: JST-2-SMD
J2, J13: 1X12_NO_SILK
J3: 1X04_1MM_RA
J4, J5, J12, J14: 1X02_NO_SILK
J6: USB-MICROB-PTH-MILL
J7, J9: 1X07_NO_SILK
J8: CORTEX_DEBUG_PTH; 2X5-PTH-1.27MM
LOGO1: SFE_LOGO_NAME.2_INCH; SFE_LOGO_NAME_.2
LOGO2: OSHW-LOGOS; OSHW-LOGO-S
R1, R2: 27; 0603
R3, R6, R10: 1k; 0603
R4, R7: 10k; 0603
R5: 2.0k; 0603
R8, R9: 2.2k; 0603
S1: RESET; TACTILE_SWITCH_SMD_RIGHT_ANGLE
S2: SWITCH_SPST_SMD_A
S3: BOOTLOAD; TACTILE_SWITCH_SMD_RIGHT_ANGLE
U1: MDBT50Q
U2: MCP73831; SOT23-5
U3: 3.3V; SOT23-5
U$1: 3V316
U$2: 130
U$3: RST19
U$4: ON1
U$5: CHG26
U$6: PWR27
U$7: GND17
U$8: QWIIC#LOGO#JPG
U$9: 20
U$10: 31
U$11: 292
U$12: 313
U$13: 3V30
U$14: 285
U$15: 521
U$16: 421
U$17: HTTP###SFE#IO#T8200
U$18: #RST6
U$19: GND7
U$20: VIN8
U$21: 1022
U$22: 916
U$23: 2111
U$24: 1912
U$25: 1713
U$26: 1522
U$27: VIN19
U$28: 70
U$29: NRF52840_MINI_BREAKOUT0
U$30: GND6
U$31: 27
U$32: 36
U$33: SWD0
U$34: 315
U$35: 300
U$36: 301
U$37: 293
U$38: 108
U$39: 51
U$40: 40
U$41: 97
U$42: 236
U$43: 200
U$44: 225
U$45: 221
U$46: 214
U$47: 203
U$48: 192
U$49: 151
U$50: 170
U$51: RST1
U$52: ANALOG2
U$53: 232
U$54: SCL#114
U$55: SDA#83
U$56: IO2
U$57: CLK1
U$58: OFF2
Y1: 32.768kHz; CRYSTAL-SMD-3.2X1.5MM

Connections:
3.3V: C1.1, C2.1, C4.1, C9.1, J2.9, J3.2, J8.1, R4.2, R7.2, R8.2, R9.2, R10.2, U1.28, U1.30, U3.5
D+: R1.2, U1.35
D+_CON: J6.D+, R1.1
D-: R2.2, U1.34
D-_CON: J6.D-, R2.1
GND: C1.2, C2.2, C3.1, C4.2, C5.2, C6.2, C7.1, C8.2, C9.2, C10.2, C11.2, D1.C, D6.C, J1.1, J2.11, J3.1, J6.GND, J8.3, J8.5, J8.9, J9.1, J9.2, J9.3, J9.4, J9.5, J9.6, J9.7, J12.1, J13.1, J13.2, J13.3, J13.4, J13.5, J13.6, J13.7, J13.8, J13.9, J13.10, J13.11, J13.12, J14.1, J14.2, R5.1, S1.1, S2.1, S3.1, U1.1, U1.2, U1.15, U1.33, U1.55, U2.2, U3.2
unnamed: R5.2, U2.5
unnamed: D2.C, R6.2
unnamed: R6.1, U2.1
unnamed: D1.A, R3.1
unnamed: D6.A, R10.1
P0.02/AIN0: J2.1, U1.11
P0.03/AIN1: J2.2, U1.9
P0.04/AIN2: J2.8, U1.20
P0.05/AIN3: J2.7, U1.21
P0.07: R3.2, U1.23
P0.08: J3.3, R8.1, U1.24
P0.09/NFC1: C11.1, J7.2, U1.52
P0.10/NFC2: C10.1, J7.1, U1.54
P0.11: J3.4, R9.1, U1.27
P0.13: R7.1, S3.2, U1.37
P0.15: J5.1, U1.39
P0.17: J5.2, U1.41
P0.19: J7.7, U1.42
P0.20: J7.6, U1.44
P0.21: J7.5, U1.43
P0.22: J7.4, U1.46
P0.23: J7.3, U1.45
P0.28/AIN4: J2.6, U1.13
P0.29/AIN5: J2.5, U1.10
P0.30/AIN6: J2.4, U1.14
P0.31/AIN7: J2.3, U1.12
SHIELD: J6.SHIELD, J6.SHIELD2, J6.SHIELD3, J6.SHIELD4, J6.SHIELD5, J6.SHIELD6, J6.SHIELD7, J6.SHIELD8, J6.SHIELD9, J6.SHIELD10
SWDCLK: J4.2, J8.4, U1.53
SWDIO: J4.1, J8.2, U1.51
VIN: C8.1, D3.C, D4.C, J2.12, S2.3, U3.1
VREG_EN: S2.2, U3.3
V_BATT: C6.1, D4.A, J1.2, J12.2, U2.3
V_USB: C5.1, D2.A, D3.A, J6.VBUS, U1.32, U2.4
XL1: C3.2, U1.17, Y1.P$2
XL2: C7.2, U1.18, Y1.P$1
~RESET: J2.10, J8.10, R4.1, S1.2, U1.40

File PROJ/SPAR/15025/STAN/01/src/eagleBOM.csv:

"Part";"Value";"Device";"Package";"Description";"PROD_ID";"SF_ID";"SF_SKU";"VALUE";
"C1";"10uF";"10UF-0603-6.3V-20%";"0603";"10.0µF ceramic capacitors";"CAP-11015";"";"";"10uF";
"C2";"0.1uF";"0.1UF-0603-25V-(+80/-20%)";"0603";"0.1µF ceramic capacitors";"CAP-00810";"";"";"0.1uF";
"C3";"15pF";"15PF-0603-50V-5%";"0603";"15pF ceramic capacitors";"CAP-07881";"";"";"15pF";
"C4";"10uF";"10UF-0603-6.3V-20%";"0603";"10.0µF ceramic capacitors";"CAP-11015";"";"";"10uF";
"C5";"4.7uF";"4.7UF-0603-6.3V-(10%)";"0603";"4.7µF ceramic capacitors";"CAP-08280";"";"";"4.7uF";
"C6";"4.7uF";"4.7UF-0603-6.3V-(10%)";"0603";"4.7µF ceramic capacitors";"CAP-08280";"";"";"4.7uF";
"C7";"15pF";"15PF-0603-50V-5%";"0603";"15pF ceramic capacitors";"CAP-07881";"";"";"15pF";
"C8";"1.0uF";"1.0UF-0603-16V-10%";"0603";"1µF ceramic capacitors";"CAP-00868";"";"";"1.0uF";
"C9";"1.0uF";"1.0UF-0603-16V-10%";"0603";"1µF ceramic capacitors";"CAP-00868";"";"";"1.0uF";
"C10";"DNP";"270PF-0603-50V-5%";"0603";"270pF/0.27nF ceramic capacitors";"CAP-13339";"";"";"270PF";
"C11";"DNP";"270PF-0603-50V-5%";"0603";"270pF/0.27nF ceramic capacitors";"CAP-13339";"";"";"270PF";
"D1";"BLUE";"LED-BLUE0603";"LED-0603";"Blue SMD LED";"DIO-08575";"";"";"BLUE";
"D2";"Yellow";"LED-YELLOW0603";"LED-0603";"Yellow SMD LED";"DIO-09003";"";"";"Yellow";
"D3";"1A/23V/620mV";"DIODE-SCHOTTKY-BAT20J";"SOD-323";"Schottky diode";"DIO-11623";"";"";"1A/23V/620mV";
"D4";"1A/23V/620mV";"DIODE-SCHOTTKY-BAT20J";"SOD-323";"Schottky diode";"DIO-11623";"";"";"1A/23V/620mV";
"D6";"RED";"LED-RED0603";"LED-0603";"Red SMD LED";"DIO-00819";"";"";"RED";
"FD1";"FIDUCIALUFIDUCIAL";"FIDUCIALUFIDUCIAL";"FIDUCIAL-MICRO";"Fiducial Alignment Points";"";"";"";"";
"FD2";"FIDUCIALUFIDUCIAL";"FIDUCIALUFIDUCIAL";"FIDUCIAL-MICRO";"Fiducial Alignment Points";"";"";"";"";
"FD3";"FIDUCIALUFIDUCIAL";"FIDUCIALUFIDUCIAL";"FIDUCIAL-MICRO";"Fiducial Alignment Points";"";"";"";"";
"FD4";"FIDUCIALUFIDUCIAL";"FIDUCIALUFIDUCIAL";"FIDUCIAL-MICRO";"Fiducial Alignment Points";"";"";"";"";
"FRAME1";"FRAME-LETTER";"FRAME-LETTER";"CREATIVE_COMMONS";"Schematic Frame - Letter";"";"";"";"";
"J1";"";"JST_2MM_MALESMD";"JST-2-SMD";"JST 2MM MALE RA CONNECTOR";"CONN-11443";"PRT-08612";"";"";
"J2";"";"CONN_12NO_SILK";"1X12_NO_SILK";"Multi connection point. Often used as Generic Header-pin footprint for 0.1 inch spaced/style header connections";"";"";"";"";
"J3";"";"QWIIC_CONNECTORJS-1MM";"1X04_1MM_RA";"SparkFun I2C Standard Qwiic Connector";"CONN-13694";"";"";"";
"J4";"";"CONN_021X02_NO_SILK";"1X02_NO_SILK";"Multi connection point. Often used as Generic Header-pin footprint for 0.1 inch spaced/style header connections";"";"";"";"";
"J5";"";"CONN_021X02_NO_SILK";"1X02_NO_SILK";"Multi connection point. Often used as Generic Header-pin footprint for 0.1 inch spaced/style header connections";"";"";"";"";
"J6";"";"USB_MICRO-B_HALF_PTH_MILL";"USB-MICROB-PTH-MILL";"USB Type Micro-B Connector";"CONN-13711";"";"";"";
"J7";"";"CONN_07NO_SILK";"1X07_NO_SILK";"Multi connection point. Often used as Generic Header-pin footprint for 0.1 inch spaced/style header connections";"";"";"";"";
"J8";"CORTEX_DEBUG_PTH";"CORTEX_DEBUG_PTH";"2X5-PTH-1.27MM";"Cortex Debug Connector - 10 pin";"";"";"";"";
"J9";"";"CONN_07NO_SILK";"1X07_NO_SILK";"Multi connection point. Often used as Generic Header-pin footprint for 0.1 inch spaced/style header connections";"";"";"";"";
"J12";"";"CONN_021X02_NO_SILK";"1X02_NO_SILK";"Multi connection point. Often used as Generic Header-pin footprint for 0.1 inch spaced/style header connections";"";"";"";"";
"J13";"";"CONN_12NO_SILK";"1X12_NO_SILK";"Multi connection point. Often used as Generic Header-pin footprint for 0.1 inch spaced/style header connections";"";"";"";"";
"J14";"";"CONN_021X02_NO_SILK";"1X02_NO_SILK";"Multi connection point. Often used as Generic Header-pin footprint for 0.1 inch spaced/style header connections";"";"";"";"";
"LOGO1";"SFE_LOGO_NAME.2_INCH";"SFE_LOGO_NAME.2_INCH";"SFE_LOGO_NAME_.2";"SparkFun Font Logo";"";"";"";"";
"LOGO2";"OSHW-LOGOS";"OSHW-LOGOS";"OSHW-LOGO-S";"Open-Source Hardware (OSHW) Logo";"";"";"";"";
"R1";"27";"27OHM-0603-1/10W-1%";"0603";"27Ω resistor";"RES-09334";"";"";"27";
"R2";"27";"27OHM-0603-1/10W-1%";"0603";"27Ω resistor";"RES-09334";"";"";"27";
"R3";"1k";"1KOHM-0603-1/10W-1%";"0603";"1kΩ resistor";"RES-07856";"";"";"1k";
"R4";"10k";"10KOHM-0603-1/10W-1%";"0603";"10kΩ resistor";"RES-00824";"";"";"10k";
"R5";"2.0k";"2.0KOHM-0603-1/10W-5%";"0603";"2kΩ resistor";"RES-08296";"";"";"2.0k";
"R6";"1k";"1KOHM-0603-1/10W-1%";"0603";"1kΩ resistor";"RES-07856";"";"";"1k";
"R7";"10k";"10KOHM-0603-1/10W-1%";"0603";"10kΩ resistor";"RES-00824";"";"";"10k";
"R8";"2.2k";"2.2KOHM-0603-1/10W-1%";"0603";"2.2kΩ resistor";"RES-08272";"";"";"2.2k";
"R9";"2.2k";"2.2KOHM-0603-1/10W-1%";"0603";"2.2kΩ resistor";"RES-08272";"";"";"2.2k";
"R10";"1k";"1KOHM-0603-1/10W-1%";"0603";"1kΩ resistor";"RES-07856";"";"";"1k";
"S1";"RESET";"MOMENTARY-SWITCH-SPST-SMD-RIGHT-ANGLE";"TACTILE_SWITCH_SMD_RIGHT_ANGLE";"Momentary Switch (Pushbutton) - SPST";"COMP-12265";"";"";"";
"S2";"";"SWITCH-SPDT-SMD-RIGHT-ANGLE";"SWITCH_SPST_SMD_A";"Single Pole, Double Throw (SPDT) Switch";"SWCH-10651";"";"COM-10860";"";
"S3";"BOOTLOAD";"MOMENTARY-SWITCH-SPST-SMD-RIGHT-ANGLE";"TACTILE_SWITCH_SMD_RIGHT_ANGLE";"Momentary Switch (Pushbutton) - SPST";"COMP-12265";"";"";"";
"U1";"MDBT50Q";"MDBT50Q";"MDBT50Q";"";"IC-14109";"";"";"";
"U2";"MCP73831";"MCP73831";"SOT23-5";"MCP73831T Li-Ion, Li-Pol Controller";"IC-09995";"";"";"";
"U3";"3.3V";"V_REG_AP2112K-3.3V";"SOT23-5";"AP2112 - 600mA CMOS LDO Regulator w/ Enable";"VREG-12457";"";"";"3.3V";
"Y1";"32.768kHz";"CRYSTAL-32.768KHZSMD-3.2X1.5";"CRYSTAL-SMD-3.2X1.5MM";"32.768kHz Crystal";"XTAL-13062";"";"";"32.768kHz";

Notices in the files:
parts and their libraries:
HTTPS://CREATIVECOMMONS.ORG/LICENSES/BY-SA/4.0
RELEASED UNDER THE CREATIVE COMMONS ATTRIBUTION SHARE-ALIKE 4.0 LICENSE
HTTPS://CREATIVECOMMONS.ORG/LICENSES/BY-SA/3.0
RELEASED UNDER THE CREATIVE COMMONS ATTRIBUTION SHARE-ALIKE 3.0 LICENSE
